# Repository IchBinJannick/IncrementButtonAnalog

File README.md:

# IncrementButtonAnalog

### Features:

- [ ] Button to increment number
- [ ] Display to show current number
- [ ] sleep mode:
  - state changes → save in EEPROM
  - no activity → Sleep Mode after x seconds
  - wake up → read state from EEPROM

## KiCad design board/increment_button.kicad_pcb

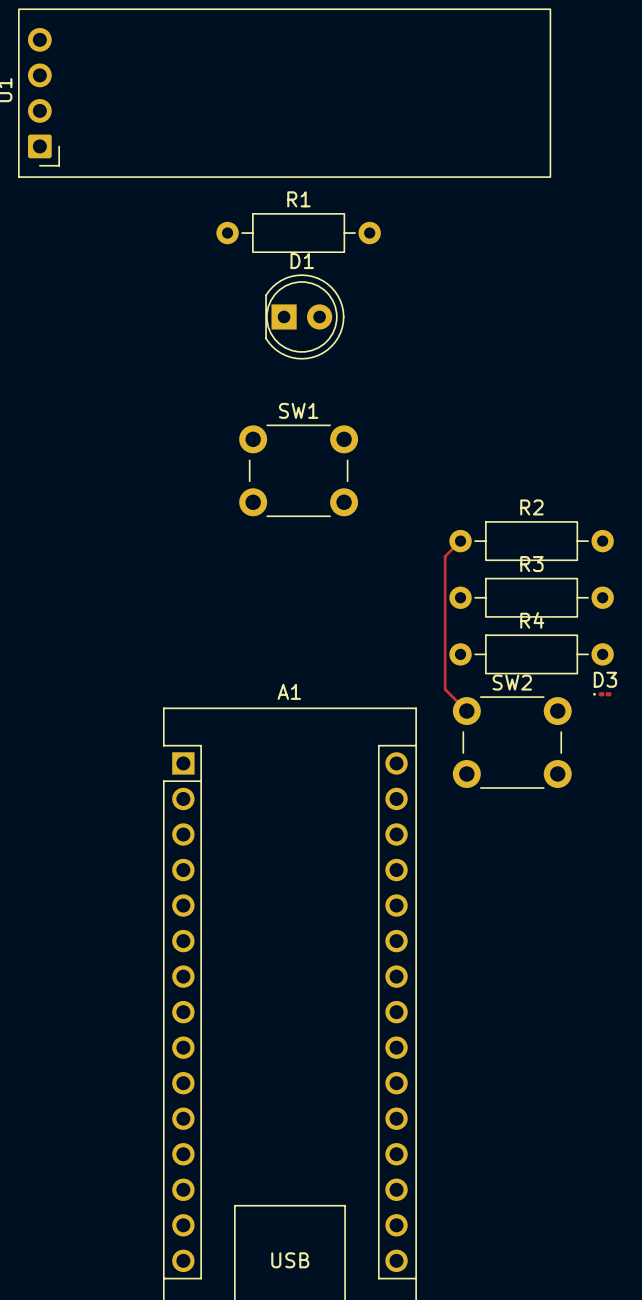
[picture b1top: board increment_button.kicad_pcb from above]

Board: 2 copper layers, 10 parts (0 on the bottom side), 9 nets.

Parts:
A1: Arduino_Nano_v2.x; Arduino_Nano
D1: LED; LED_D5.0mm
D3: LED; LED_01005_0402Metric
R1, R2, R3, R4: R; R_Axial_DIN0207_L6.3mm_D2.5mm_P10.16mm_Horizontal
SW1, SW2: SW_Push_SPDT; SW_PUSH_6mm
U1: ER_OLEDM0.91_1x-I2C

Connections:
unnamed: A1.17 (3V3), R1.2, R2.2, U1.2 (VCC)
unnamed: A1.23 (A4), U1.4 (SDA)
unnamed: A1.24 (A5), U1.3 (SCL)
unnamed: A1.5 (D2), D1.2 (A), R3.1
unnamed: A1.6 (D3), SW1.2 (B)
unnamed: A1.7 (D4), SW2.2 (B)
unnamed: A1.4 (GND), D3.1 (K), D3.2 (A), U1.1 (GND)
unnamed: R1.1, SW1.1 (A)
unnamed: R2.1, SW2.1 (A)

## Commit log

2026-05-23 initial base setup
2026-05-23 edited README
2026-05-23 added schematics and pcb
2026-05-29 changed sch
2026-05-29 finished counting logic
2026-05-29 finished code
2026-06-09 some bullshit
2026-06-09 removed 2 wires in test.kicad_sch
2026-06-09 added 3 wires, modified 1 wire in test.kicad_sch
